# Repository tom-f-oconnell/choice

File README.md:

### Installation
1. [Install ROS Kinetic](http://wiki.ros.org/kinetic/Installation) on a supported operating system.  
   - Tested on [Ubuntu 16.04](https://www.ubuntu.com/download/desktop).
   - You can install Ubuntu alongside Windows with minimal effort.
   - Other ROS versions may work, but tested with Kinetic.
   - You only need `ros-kinetic-ros-base`.
      - You do *NOT* need everything in `ros-kinetic-desktop-full`, and it takes more disk space and install time.

2. Install the catkin packages.
   See ROS [tutorial on making a catkin workspace](http://wiki.ros.org/catkin/Tutorials/create_a_workspace).

   If you have not already, add a line to your `~/.bashrc` that loads the development setup script (that catkin generates), such as:
   ```
   source <your_catkin_workspace>/devel/setup.bash
   ```

   Then this should install all the packages you need:
   ```
   cd <your_catkin_workspace>/src
   git clone https://github.com/tom-f-oconnell/multi_tracker.git
   git clone https://github.com/tom-f-oconnell/usb_cam.git
   git clone https://github.com/tom-f-oconnell/rosserial.git
   git clone https://github.com/tom-f-oconnell/metatools.git
   git clone https://github.com/tom-f-oconnell/stimuli.git
   git clone https://github.com/tom-f-oconnell/choice.git
   cd <your_catkin_workspace>
   catkin_make
   . ~/.bashrc
   ```

   The last line loads `<your_catkin_workspace>/devel/setup.bash` because of the line you added to your `~/.bashrc` in the previous step.

   On all of the computers in the Hong lab, the catkin workspace can be found at `~/catkin`, for whichever user account was used to run the experiments.

   Currently, only installation from source is supported. In the future, I would like to make this installable as a ROS package via apt, but that would likely also require the same of `multi_tracker`, and there are some technical reasons that won't be possible right now with ROS Kinetic.

3. Upload the firmware to an Arduino MEGA
   1. Download and unzip Arduino to a path you will remember, or locate it if already installed.
      - Version ~1.5 - 1.8.3 should definitely work. Nearby versions almost certainly also will. You should get error messages when compiling if things do not work, and if this is the case you may need to use a different version of Arduino.
      - Arduino older than or equal to 1.0 will likely not work.
      - I unzipped Arduino to my home directory, which came out as as `~/arduino-1.8.3`, which I will use as an example.
   2. `cd ~/arduino-1.8.3/libraries` (or wherever your Arduino is installed)
   3. `rm -rf ros_lib` (in case some libraries have already been generated)
   4. `rosrun rosserial_arduino make_libraries.py .`
   5. Symlink to `stimuli` and `multishock` libraries. You only need
      `multishock` if uploading code that relies on the shift-register based
      shock control hardware.

      (still from `~/arduino-1.8.3/libraries`)
      ```
      ln -s ~/catkin/src/stimuli/arduino/libraries/stimuli
      ln -s ~/catkin/src/choice/arduino/libraries/multishock
      ```

   6. If you Arduino IDE was open, close and re-open it.
      - *Make sure that you are opening the same version of Arduino you installed the libraries for.* It is easier to only have one version of Arduino installed at any given time to avoid these conflicts.

   7. Add your user to the `dialout` group (if on Ubuntu), to be able to upload code.
      - `sudo adduser <username> dialout`
      - Log out and back in for the change to take effect

   8. Connect your Arduino MEGA to the computer.
      - Arduino's with less memory will currently **NOT** work, as there is considerable overhead in the generated ROS libraries.

   9. Upload code 
       
      For the basic stimulus delivery, open `File->Examples->stimuli->stimuli` 
      In the Arduino IDE, under the `Tools` menu:
      - Select appropriate port
         - Usually `/dev/ttyUSBX`, where `X` could vary. `/dev/ttyACMX` may also work. It is never the one like `/dev/ttyS0`.
         - May have the correct board model in parentheses after the port name
      - Select appropriate board (probably `Arduino/Genuino Mega or Mega 2560`)
      - Press the Upload button in the top left of the IDE
         - It looks like a circle with a righward arrow in it.
      - If the TX / RX lights flash on the Arduino, and the Upload seems to finish, you should be good to go.

4. *(Optional)* Set an alias for running `roslaunch` with a different `ROS_HOME` environment variable.

To load the configuration files from (and to save the output directory to) the current directory, I prefix the `roslaunch choice choice.launch` command with `ROS_HOME=``pwd```. To make all `roslaunch` invokations behave this way, which works for my purposes, you can make an alias for `roslaunch`.

If you don't already have a ~/.bash_aliases file, you can create one by opening it in a text editor, otherwise just open the file you already have. Add a line that says:
```
alias roslaunch='ROS_HOME=`pwd` roslaunch'
```

Save and close the file, and reload your terminal environment by typing `. ~/.bashrc`, or opening a new terminal. Now you can just type `roslaunch choice choice.launch`, and it will load configuration input from the current directory and save output there as well.

### Manufacture

TODO link to a readme in the design folder / wiki?

### Running an experiment

#### Requirements
The current directory has at least the following configuration files:
##### For tracking
- tracker_parameters.yaml
- roi_finder.yaml
- delta_video_parameters.yaml

- If running the tracking in real-time, also:
   - liveviewer_parameters.yaml
   - data_association_parameters.yaml
   - kalman_parameters.py

##### For stimulus
- stimulus_parameters.yaml

Depending on the camera you are using, you may also want to include parameters for your camera node, which you will have to load separately. There are some examples in the `multi_tracker` repository.

To copy templates for each of these configuration files to your current directory:
```
rosrun choice copy_configs.py
```

##### To set the length of the experiment
In the `stimulus_parameters.yaml` file, set the parameters starting at `olf/training_blocks` and ending at `olf/beyond_posttest_s` to appropriate values.

In `tracker_parameters.yaml`, set `multi_tracker/record_length_hours` to -1, so
that the length of the recording is determined by the stimulus presentation.

#### To run a full experiment with real-time tracking on the same computer.
Requires a computer with adequate memory and processor.
```
roslaunch choice choice.launch
```

##### Errors (red text)
The only error message that is normal during startup is one along the lines of `Parameter stimulus_arduino/debug does not exist`. Another other red text means something is likely not working, and you should not ignore it.

##### Warnings (yellow text)
`Failed to get param: timeout expired` is normal, as long as the program ultimately stops 
emitting these warnings. You should be aware of the reasons other warnings occur. 
Contact Tom with any questions.

#### To run an experiment saving a background subtracted video in a ROS bag file, for offline tracking.
Less hardware demands.
```
roslaunch choice choice.launch video_only:=True
```

##### Possible problems

If you run `rosparam list` before starting an experiment, you should see
`ERROR: Unable to communicate with master!`, otherwise, the existing parameters
can misconfigure any experiments you try to run.

First, check it isn't a valid experiment being run on another account, if you're
sharing the computer. If not, you should be able to stop the existing `roscore`
process with:
```
sudo pkill rosmaster
```

After this command, you another `rosparam list` should give you
```
ERROR: Unable to communicate with master!
```

### Stimulus Validation

To run the stimulus presentation that would happen during an experiment, but without any 
recording or tracking. For measurement / verification / PID purposes.
```
roslaunch choice choice.launch stimuli_only:=True
```

To run simpler pulse trains of a given duration, without changing the code on the Arduino. 
This launch file will also look for a `stimulus_parameters.yaml` file in the same path, but
with slightly different parameters.
```
roslaunch stimuli pid.launch seconds:=30
```

See [this repo](https://github.com/tom-f-oconnell/stimuli#validation) for more information 
on the parameters and launch file arguments for `pid.launch`.

To test the valves (I run this before and after each experiment, to make sure no connections came loose. With more robust electronics this might be less of a concern.)
- The number of the pin to be switched will be printed in the terminal you run the launch file from.
- I attach higher pressure air to all valves and check manually for air flow at each pin that should be switched.
```
roslaunch stimuli test_valves.launch
```

Press `<Ctrl>-C` to stop the `test_valves.launch` file.

### Offline tracking

#### Requirements
- The environment variable `DATA_DIR` is set to a path you will keep your data directories beneath.
   - I organize my experiment directories as grandchildren of `DATA_DIR`, grouping them as I see fit with directories (of arbitrary names) just beneath `DATA_DIR`.
   - To test that this is set, you can run `echo $DATA_DIR`, and the path should be printed.
   - To set this:

     Add a line to your `~/.bashrc` file like:

     ```
     export DATA_DIR="<full_path_to_data_directory>"
     ```

     For instance, mine has this line:
     ```
     export DATA_DIR="$HOME/data"
     ```

     Then, either start a new terminal, or run `. ~/.bashrc`, so that the change in the environment variable takes effect.

- `$DATA_DIR/retracked` exists and has all of the configuration files required for tracking (see requirements for running an experiment above)
- All of the installation instructions for at least ROS and the `multi_tracker` package are done.

On any computer satisfying these requirements, run:
```
rosrun multi_tracker retrack_ros <experiment_directory> <decimal_valued_rate>
```

The `<decimal_valued_rate>` can be set as high as does not produce a stream of warning messages that does not improve until the tracking finishes.  If the computer appears to be straining, you may also want to decrease the rate.  If you want to also employ more limited computers for tracking lots of data, you are also able to decrease the rate beneath 1.0 if necessary.

The default rate is currently 0.8, if no rate is provided. Our analysis workstations can track up to a rate of 4.0 - 5.0, with little issue.

The `<experiment_directory>` can be any of:
- ~~a path to a valid directory~~
- ~~a file within a valid directory~~
- the name of a subdirectory beneath `$DATA_DIR`, if the `DATA_DIR` environment variable is set
   - the way this script currently finds the output path, it requires `DATA_DIR`, so you should use this option for now.

A valid directory has:
- at a minimum:
   - a name in the `YYYYMMDD_HHMMSS` format
   - a bag file
   - any background PNGs that were in the same directory
   - a file with the ROIs called `compressor_rois_<experiment_id>.yaml`
- ideally, all files generated during acquisition, including also:
   - a `*_parameters.yaml` file
   - a `*_stimuli.p` file

#### Example
```
rosrun multi_tracker retrack_ros 20170930_164433 2.0
```

In this example, `DATA_DIR` was set with a line in my `~/.bashrc` file as:
```
export DATA_DIR="$HOME/data"
```
and `/home/tom/data/20170920/20170930_164433` was a valid directory. Note that `20170930_164433` was not a direct child directory of `DATA_DIR`. The code may currently expect the `<experiment_directory>` to be a granchild of `DATA_DIR`, if this option is selected.

#### Output
After running the tracking, the valid directory you provided as input will also have:
- An HDF5 file with a the variables the tracker is estimating, over time
   - The `position_x` and `position_y`

#### Copying data from acquisition to tracking / analysis computer

You are of course free to copy the files via other means. This may just end up being convenient.

#### Requirements
- Both computers have internet access
- The computer you are trying to connect TO has an SSH server installed and running
   - Look up how to install OpenSSH server for the operating system you are using if you need to do this.

```
rsync -auvPzr <folder_with_data> user@<server_ip_address>:~/<place_to_put_it>
```

The rsync command with those flags seems not to work if you include a trailing slash after the `<folder_with_data>` name.

#### Example
```
rsync -auvPzr ~/data/. tom@gerty:~/data
```
This example will recursively copy all subdirectories of data, and I keep all my experiment directories nested within here.

#### Known bugs + workarounds
If you notice your computer working harder than it should when the acquisition / tracking should otherwise have terminated, you can run `top` or some other process manager, and check for a handful of processes, owned by the same user that ran the launch file, with names including:
- `play`
- `record`
- `python`
- `<something>launch` ?

And assuming you are OK killing all ROS processes currently running on your computer, you can try running:
- `killall roscore`
- `killall roslaunch`
- `killall play`

Under some circumstances, you may also want to kill all python processes owned by the user that started the ROS processes, with `killall python`.

### Analysis
#### Requirements
(To be added )
- `DATA_DIR` is set as in offline tracking instructions.
- `choice` and `multi_tracker` are installed as above (though you don't technically need all of ROS)
- The experiments you want to analyze together have their data folders grouped within an immediate subdirectory of `$DATA_DIR/retracked`.
   - If your tracking output comes from real-time tracking, it does not need to be treated differently, apart from copying it to a subdirectory beneath `$DATA_DIR/retracked`.
- The `ruamel.yaml` package, which you should be able to get via:
   ```
   cd <choice>
   pip install -r requirements.txt
   ```
   Again, if you need root access to install via `pip`, use `sudo` as above.

#### Running
```
rosrun choice choice_analysis <subdirectory>
```

If, across all analysis runs *that have used this folder as input*, you have not already labelled all experiments as either good or needing rejection for some reason, a GUI should open asking you to label the traces appropriately. See the terminal output for which keys correspond to which labels.

The output of this labelling should be saved as `$DATA_DIR/retracked/<subdirectory>/analysis_rejects.yaml`. It is human readable, and you can edit it by hand in a text editor if you want to change something. If you want to start the labelling over, feel free to delete or move / rename `analysis_rejects.yaml`.

Currently, if you want labels to apply across groupings of your data, (across analysis runs with different subdirectories as input) you will need to manually merge the `analysis_rejects.yaml` text files.

#### Output

Within the `$DATA_DIR/retracked/<subdirectory>`, you should find a number of files in a graphics format (svg by default). For each odor, each reject category, and each preference metric (fraction of time spent and "decision bias"), you will find:
- `<metric>.svg`
   - For pooled data of all non-rejects, across all odors.
- `<odor>_<metric>.svg` (or .other_graphic_format, like .png)
   - For pooled data of all non-rejects, within an odor.
- `<reject_category>_<metric>.svg`
   - For data of all rejects of a certain label / category, pooled across odors

There will also be text output, in the terminal in which you ran the analysis, describing the metrics within and across odors, and the fraction of flies in each reject category.

### Updating code

If you have made any changes to your local copies of these repositories that you would like to keep, look up `git stash` and proceed with caution, otherwise:

```
roscd multi_tracker
git pull
roscd choice
git pull
```

Then, repeat the instructions for installing catkin packages above, which should look like:
```
cd <catkin_workspace>
catkin_make
. ~/.bashrc
```

This, again, requires that you have a line in your `~/.bashrc` that "sources" (loads) the file `<catkin_ws>/devel/setup.bash`, or else the line `. ~/.bashrc` will not necessarily apply all updates that have been made to the code.

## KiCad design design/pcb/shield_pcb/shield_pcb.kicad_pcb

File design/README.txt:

If any .svg or .fcstd files are newer than files of the same name with a
different extension (should be .eps and .stl, respectively), then you may want
to delete those .eps and .stl files and re-generate them from the newer source
files before cutting / printing the parts.

SVGs are Inkscape SVGs. Generally I would export these as EPS and then load them
on the computer connected to the laser cutter in Coreldraw.  In Coreldraw, I
would convert all lines to "Hairline" , as this was required for any lines you'd
like to cut (<0.0001" should be treated the same, but it is harder to work with
while designing).

.fcstd files should be openable with FreeCAD. The software is getting a lot
better, so it is worth getting the most recent version from the PPA (you can
look up how to do this). I generally used version 0.17. To export STLs you have
to open the FCSTD file, select an object (on the left, the highest level node
that isn't the name of the document), and then go to File->Export and change the
output file type to STL.  I prepared gcode (instruction for the 3D printer) in
Cura, on Windows, because this is what our librarian showed me how to use.

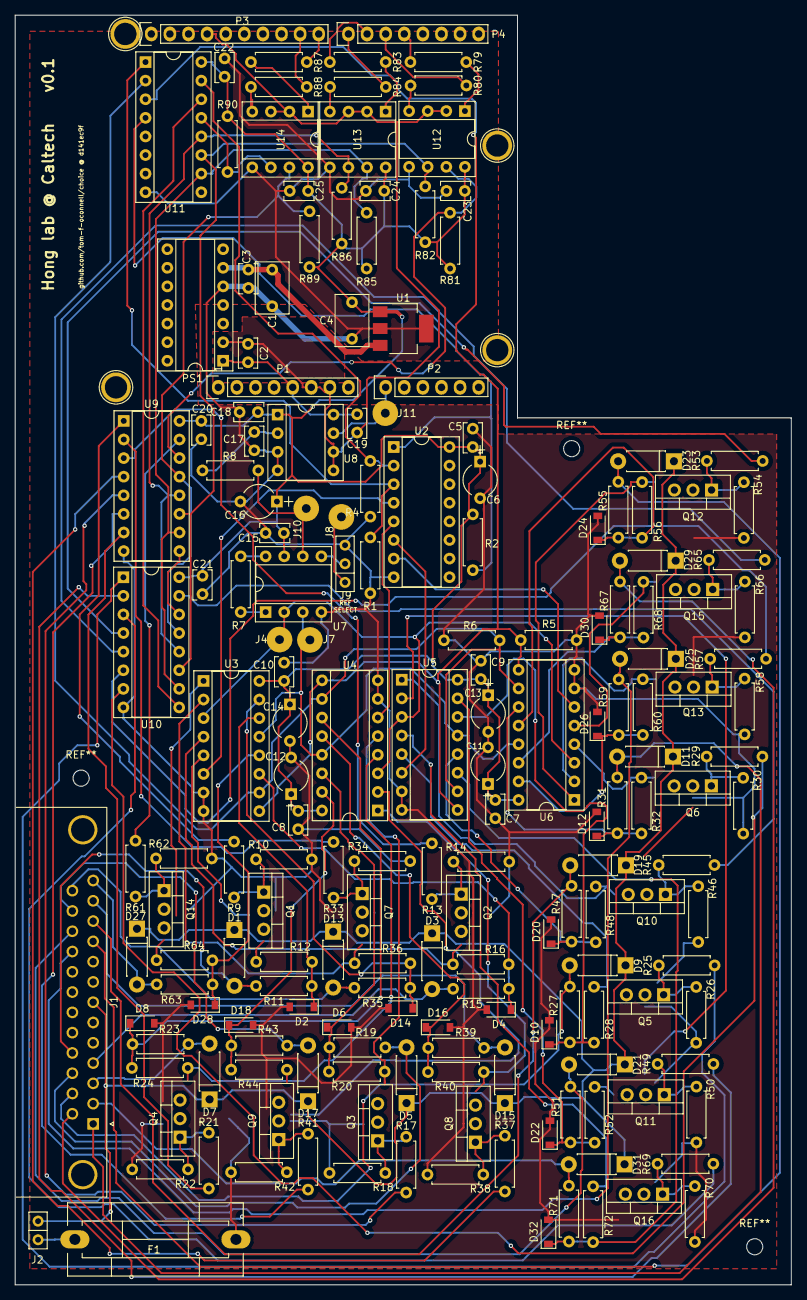
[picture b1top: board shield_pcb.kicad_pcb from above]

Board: 2 copper layers, 106.0 x 173.4 mm, 188 parts (0 on the bottom side), 125 nets.

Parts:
C1, C4: 1uF; C_Rect_L7.0mm_W4.5mm_P5.00mm
C2, C3: 2.2uF; C_Rect_L4.0mm_W2.5mm_P2.50mm
C5, C7, C8, C9, C10, C15, C18, C19, C20, C21, C22, C23, C24, C25: 0.1uF; C_Rect_L4.0mm_W2.5mm_P2.50mm
C6, C11, C12, C13, C14, C16: 10uF; CP_Radial_Tantal_D4.5mm_P5.00mm
C17: 22nF; C_Rect_L4.0mm_W2.5mm_P2.50mm
D1, D3, D5, D7, D9, D11, D13, D15, D17, D19, D21, D23, D25, D27, D29, D31: D; D_DO-41_SOD81_P7.62mm_Horizontal
D2, D4, D6, D8, D10, D12, D14, D16, D18, D20, D22, D24, D26, D28, D30, D32: MMSZ5231B; D_SOD-123
F1: Fuse; Fuseholder5x20_horiz_SemiClosed_Casing10x25mm
J1: DB25_Female; DSUB-25_Female_Horizontal_Pitch2.77x2.84mm_EdgePinOffset7.7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
J2: Screw_Terminal_01x02; SIP-2_terminal_block
J4, J7, J8, J10, J11: Conn_01x01; SolderWirePad_single_1-2mmDrill
J9: Conn_01x03_Male; SIP-3
P1: Power; Socket_Strip_Arduino_1x08
P2: Analog; Socket_Strip_Arduino_1x06
P3: Digital; Socket_Strip_Arduino_1x10
P4: Digital; Socket_Strip_Arduino_1x08
P5, P6, P7, P8: CONN_01X01; Arduino_1pin
PS1: DCP020507P; DIP-14_W7.62mm_Socket
Q1, Q2, Q3, Q4, Q5, Q6, Q7, Q8, Q9, Q10, Q11, Q12, Q13, Q14, Q15, Q16: IRL620; TO-220-3_Vertical
R1, R2, R4, R5, R6: 4.7K; R_Axial_DIN0207_L6.3mm_D2.5mm_P7.62mm_Horizontal
R7: R; R_Axial_DIN0207_L6.3mm_D2.5mm_P7.62mm_Horizontal
R8: 10; R_Axial_DIN0207_L6.3mm_D2.5mm_P7.62mm_Horizontal
R9, R13, R17, R21, R25, R29, R33, R37, R41, R45, R49, R53, R57, R61, R65, R69: 150; R_Axial_DIN0207_L6.3mm_D2.5mm_P7.62mm_Horizontal
R10, R12, R14, R16, R18, R20, R22, R24, R26, R28, R30, R32, R34, R36, R38, R40, R42, R44, R46, R48, R50, R52, R54, R56, R58, R60, R62, R64, R66, R68, R70, R72: 100K; R_Axial_DIN0207_L6.3mm_D2.5mm_P7.62mm_Horizontal
R11, R15, R19, R23, R27, R31, R35, R39, R43, R47, R51, R55, R59, R63, R67, R71: 39K; R_Axial_DIN0207_L6.3mm_D2.5mm_P7.62mm_Horizontal
R79, R80, R83, R84, R87, R88: 220; R_Axial_DIN0207_L6.3mm_D2.5mm_P7.62mm_Horizontal
R81, R82, R85, R86, R89, R90: 2.2K; R_Axial_DIN0207_L6.3mm_D2.5mm_P7.62mm_Horizontal
U1: LT1118-5; SOT-223
U2: 4556; DIP-16_W7.62mm_Socket
U3, U4, U5, U6: CD4052B; DIP-16_W7.62mm_Socket
U7: AD623; DIP-8_W7.62mm_Socket
U8: ACPL-790x; DIP-8_W7.62mm_Socket
U9, U10, U11: 74HC595; DIP-16_W7.62mm_Socket
U12, U13, U14: TLP2531; DIP-8_W7.62mm_Socket

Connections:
+5V: C2.1, C19.2, P1.5, PS1.1, U8.8
+5VA: C4.1, C5.1, C6.1, C7.1, C8.1, C9.1, C10.1, C11.1, C12.1, C13.1, C14.1, C15.1, C16.1, C18.1, C20.1, C21.1, C22.1, C23.1, C24.1, C25.1, R2.1, R81.1, R82.1, R85.1, R86.1, R89.1, R90.1, U1.1, U2.16, U3.16, U4.16, U5.16, U6.16, U7.7, U8.1, U9.16, U10.16, U11.16, U12.8, U13.8, U14.8
/1+: D28.1, R63.2, R64.1, U3.12
/1-: Q14.2, R64.2, U3.1
/2+: D2.1, R11.2, R12.1, U3.14
/2-: Q1.2, R12.2, U3.5
/3+: D14.1, R35.2, R36.1, U3.15
/3-: Q7.2, R36.2, U3.2
/4: P4.4, R79.2
/4+: D4.1, R15.2, R16.1, U3.11
/4-: Q2.2, R16.2, U3.4
/5(**): P4.3, R80.2
/5+: D16.1, R39.2, R40.1, U4.12
/5-: Q8.2, R40.2, U4.1
/6(**): P4.2, R83.2
/6+: D6.1, R19.2, R20.1, U4.14
/6-: Q3.2, R20.2, U4.5
/7: P4.1, R84.2
/7+: D18.1, R43.2, R44.1, U4.15
/7-: Q9.2, R44.2, U4.2
/8: P3.10, R87.2
/8+: D8.1, R23.2, R24.1, U4.11
/8-: Q4.2, R24.2, U4.4
/9(**): P3.9, R88.2
/9+: D20.1, R47.2, R48.1, U5.12
/9-: Q10.2, R48.2, U5.1
/10+: D10.1, R27.2, R28.1, U5.14
/10-: Q5.2, R28.2, U5.5
/11+: D22.1, R51.2, R52.1, U5.15
/11-: Q11.2, R52.2, U5.2
/12+: D32.1, R71.2, R72.1, U5.11
/12-: Q16.2, R72.2, U5.4
/13+: D24.1, R55.2, R56.1, U6.12
/13-: Q12.2, R56.2, U6.1
/14+: D30.1, R67.2, R68.1, U6.14
/14-: Q15.2, R68.2, U6.5
/15+: D26.1, R59.2, R60.1, U6.15
/15-: Q13.2, R60.2, U6.2
/16+: D12.1, R31.2, R32.1, U6.11
/16-: Q6.2, R32.2, U6.4
/A0: J11.1, P2.1, U8.7
/CA: R6.1, U3.10, U4.10, U5.10, U6.10, U11.2
/CB: R5.1, U3.9, U4.9, U5.9, U6.9, U11.3
/DA: R4.1, U2.2, U11.15
/DB: R1.1, U2.3, U11.1
/DMUX_EN: R2.2, U2.1, U11.4
/F1: D27.2, J1.13, R63.1
/F2: D1.2, J1.17, R11.1
/F3: D13.2, J1.25, R35.1
/F4: D3.2, J1.4, R15.1
/F5: D15.2, J1.12, R39.1
/F6: D5.2, J1.16, R19.1
/F7: D17.2, J1.24, R43.1
/F8: D7.2, J1.3, R23.1
/F9: D19.2, J1.11, R47.1
/F10: D9.2, J1.15, R27.1
/F11: D21.2, J1.23, R51.1
/F12: D31.2, J1.2, R71.1
/F13: D23.2, J1.10, R55.1
/F14: D29.2, J1.14, R67.1
/F15: D25.2, J1.22, R59.1
/F16: D11.2, J1.1, R31.1
/IN1: R61.2, U9.15
/IN2: R9.2, U9.1
/IN3: R33.2, U9.2
/IN4: R13.2, U9.3
/IN5: R37.2, U9.4
/IN6: R17.2, U9.5
/IN7: R41.2, U9.6
/IN8: R21.2, U9.7
/IN9: R45.2, U10.15
/IN10: R25.2, U10.1
/IN11: R49.2, U10.2
/IN12: R69.2, U10.3
/IN13: R53.2, U10.4
/IN14: R65.2, U10.5
/IN15: R57.2, U10.6
/IN16: R29.2, U10.7
/digital_input_isolation/optoisolator_with_peripherals_1/out_1: R81.2, U9.14, U12.7
/digital_input_isolation/optoisolator_with_peripherals_1/out_2: R82.2, U9.11, U10.11, U11.11, U12.6
/digital_input_isolation/optoisolator_with_peripherals_2/out_1: R85.2, U9.10, U10.10, U11.10, U13.7
/digital_input_isolation/optoisolator_with_peripherals_2/out_2: R86.2, U9.12, U10.12, U11.12, U13.6
/digital_input_isolation/optoisolator_with_peripherals_3/out_1: R89.2, U9.13, U10.13, U14.7
/digital_input_isolation/optoisolator_with_peripherals_3/out_2: R90.2, U11.13, U14.6
GND: C2.2, C19.1, P1.6, P1.7, P3.4, PS1.2, U8.5, U8.6, U12.2, U12.3, U13.2, U13.3, U14.2, U14.3
GNDA: C1.1, C3.2, C4.2, C5.2, C6.2, C7.2, C8.2, C9.2, C10.2, C11.2, C12.2, C13.2, C14.2, C15.2, C16.2, C17.2, C18.2, C20.2, C21.2, C22.2, C23.2, C24.2, C25.2, D2.2, D4.2, D6.2, D8.2, D10.2, D12.2, D14.2, D16.2, D18.2, D20.2, D22.2, D24.2, D26.2, D28.2, D30.2, D32.2, F1.1, J9.3, PS1.5, Q1.3, Q2.3, Q3.3, Q4.3, Q5.3, Q6.3, Q7.3, Q8.3, Q9.3, Q10.3, Q11.3, Q12.3, Q13.3, Q14.3, Q15.3, Q16.3, R1.2, R4.2, R5.2, R6.2, R10.2, R14.2, R18.2, R22.2, R26.2, R30.2, R34.2, R38.2, R42.2, R46.2, R50.2, R54.2, R58.2, R62.2, R66.2, R70.2, U1.2, U1.4, U2.8, U3.7, U3.8, U4.7, U4.8, U5.7, U5.8, U6.7, U6.8, U7.4, U8.3, U8.4, U9.8, U10.8, U11.8, U12.5, U13.5, U14.5
HV: D1.1, D3.1, D5.1, D7.1, D9.1, D11.1, D13.1, D15.1, D17.1, D19.1, D21.1, D23.1, D25.1, D27.1, D29.1, D31.1, J1.7, J2.1
unnamed: C1.2, C3.1, PS1.6, U1.3
unnamed: C17.1, R8.1, U8.2
unnamed: F1.2, J2.2
unnamed: J4.1, U3.3, U4.3, U5.3, U6.3, U7.2
unnamed: J7.1, U3.13, U4.13, U5.13, U6.13, U7.3
unnamed: J8.1, J9.1
unnamed: J9.2, U7.5
unnamed: J10.1, R8.2, U7.6
unnamed: Q1.1, R9.1, R10.1
unnamed: Q2.1, R13.1, R14.1
unnamed: Q3.1, R17.1, R18.1
unnamed: Q4.1, R21.1, R22.1
unnamed: Q5.1, R25.1, R26.1
unnamed: Q6.1, R29.1, R30.1
unnamed: Q7.1, R33.1, R34.1
unnamed: Q8.1, R37.1, R38.1
unnamed: Q9.1, R41.1, R42.1
unnamed: Q10.1, R45.1, R46.1
unnamed: Q11.1, R49.1, R50.1
unnamed: Q12.1, R53.1, R54.1
unnamed: Q13.1, R57.1, R58.1
unnamed: Q14.1, R61.1, R62.1
unnamed: Q15.1, R65.1, R66.1
unnamed: Q16.1, R69.1, R70.1
unnamed: R7.1, U7.1
unnamed: R7.2, U7.8
unnamed: R79.1, U12.1
unnamed: R80.1, U12.4
unnamed: R83.1, U13.1
unnamed: R84.1, U13.4
unnamed: R87.1, U14.1
unnamed: R88.1, U14.4
unnamed: U2.4, U3.6
unnamed: U2.5, U4.6
unnamed: U2.6, U5.6
unnamed: U2.7, U6.6
unnamed: U10.9, U11.14
unnamed: U9.9, U10.14

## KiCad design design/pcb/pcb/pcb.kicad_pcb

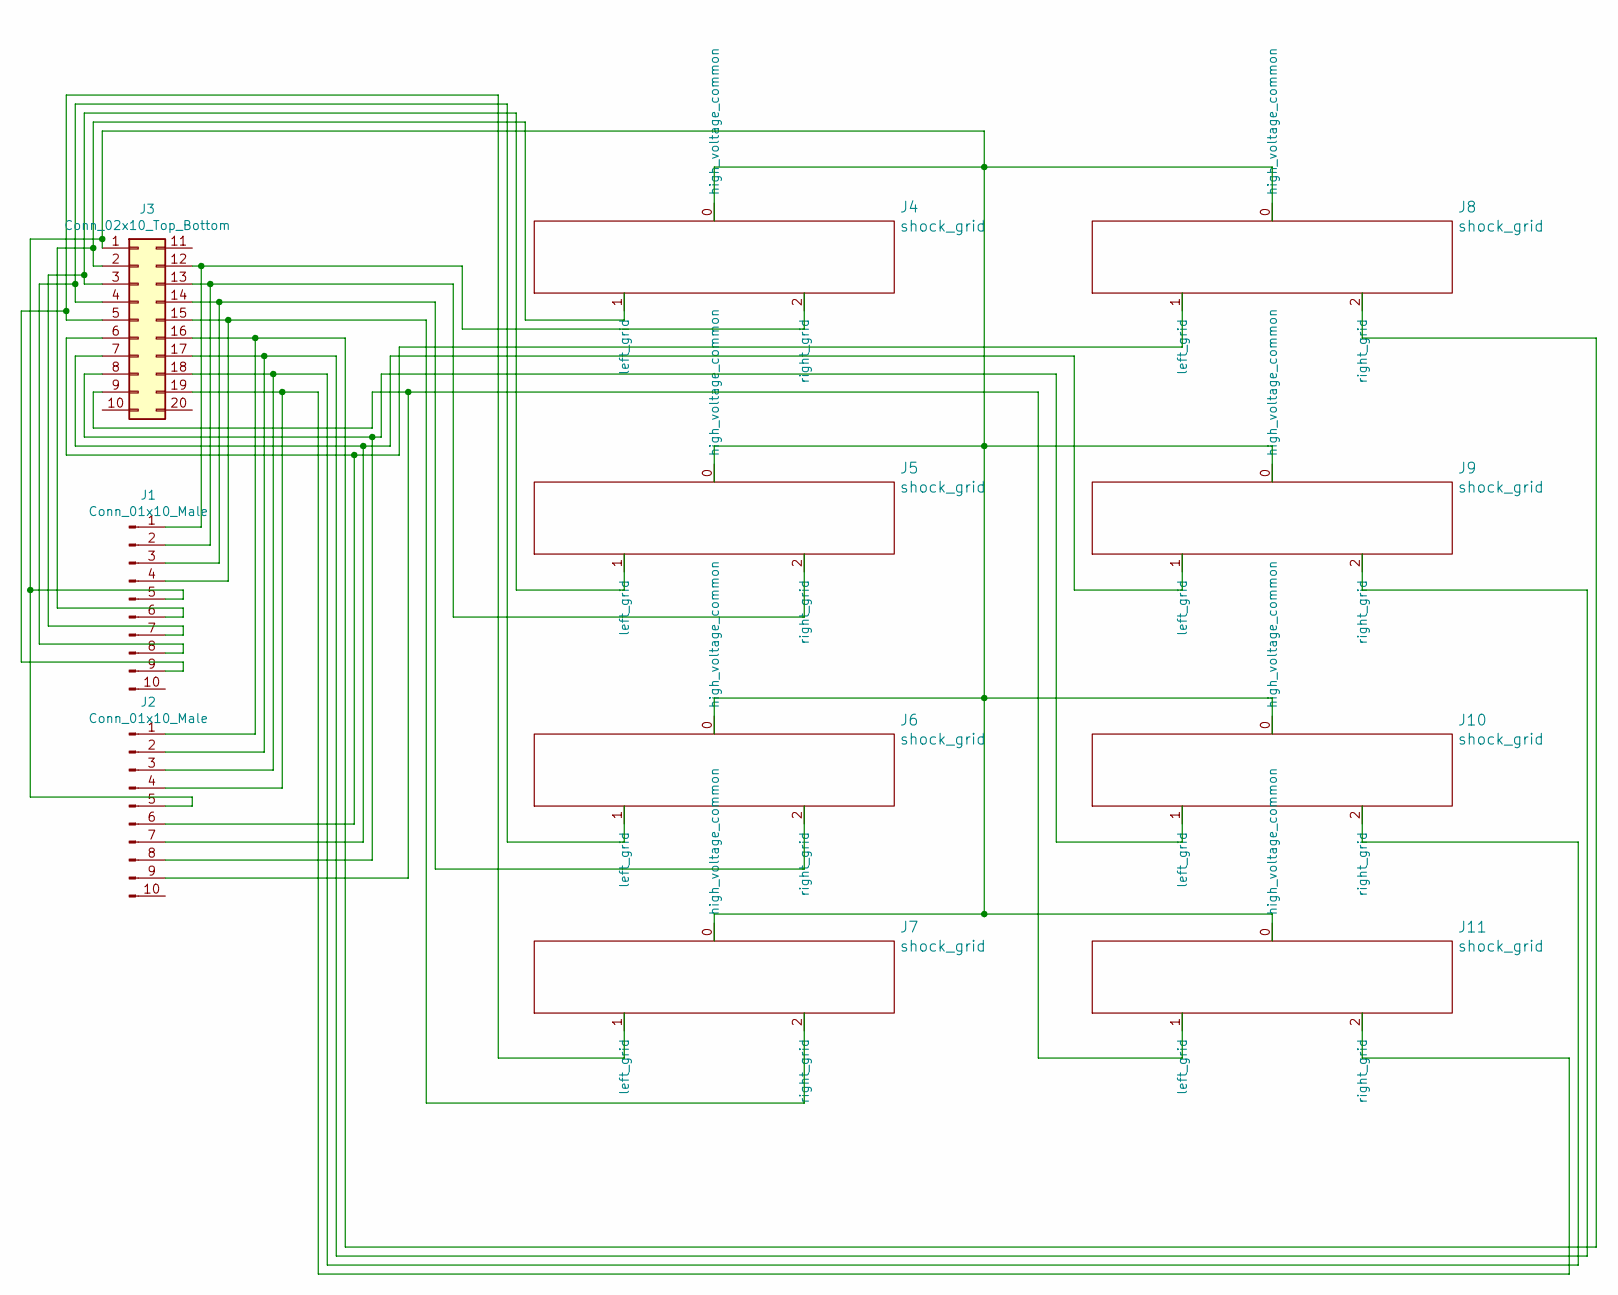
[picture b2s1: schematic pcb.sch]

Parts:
J1, J2: Conn_01x10_Male; SIP-10_2.54mm_1mm_clearance
J3: Conn_02x10_Top_Bottom; DIP-2x10_2.54mm_1mm_clearance
J4, J5, J6, J7, J8, J9, J10, J11: shock_grid; electrode

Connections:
unnamed: J1.1, J3.12, J4.2 (right_grid)
unnamed: J1.2, J3.13, J5.2 (right_grid)
unnamed: J1.3, J3.14, J6.2 (right_grid)
unnamed: J1.4, J3.15, J7.2 (right_grid)
unnamed: J1.5, J2.5, J3.1, J4.0 (high_voltage_common), J5.0 (high_voltage_common), J6.0 (high_voltage_common), J7.0 (high_voltage_common), J8.0 (high_voltage_common), J9.0 (high_voltage_common), J10.0 (high_voltage_common), J11.0 (high_voltage_common)
unnamed: J1.6, J3.2, J4.1 (left_grid)
unnamed: J1.7, J3.3, J5.1 (left_grid)
unnamed: J1.8, J3.4, J6.1 (left_grid)
unnamed: J1.9, J3.5, J7.1 (left_grid)
unnamed: J2.1, J3.16, J8.2 (right_grid)
unnamed: J2.2, J3.17, J9.2 (right_grid)
unnamed: J2.6, J3.6, J8.1 (left_grid)
unnamed: J2.7, J3.7, J9.1 (left_grid)
unnamed: J2.8, J3.8, J10.1 (left_grid)
unnamed: J2.3, J3.18, J10.2 (right_grid)
unnamed: J2.9, J3.9, J11.1 (left_grid)
unnamed: J2.4, J3.19, J11.2 (right_grid)

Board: 2 copper layers, 11 parts (0 on the bottom side), 17 nets, no tracks yet.

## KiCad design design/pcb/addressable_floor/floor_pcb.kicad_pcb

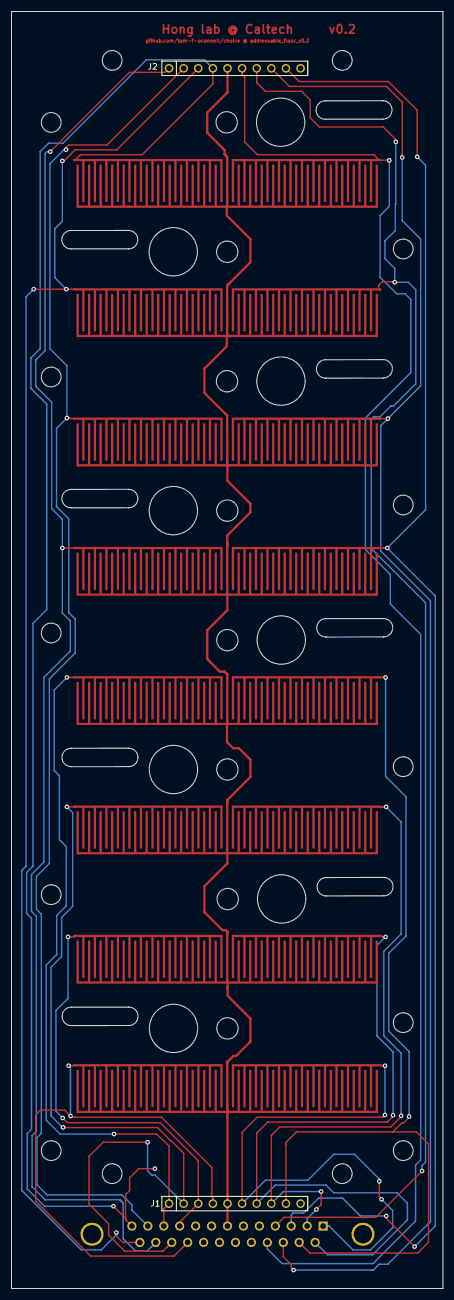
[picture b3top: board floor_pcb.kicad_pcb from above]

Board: 2 copper layers, 75.0 x 222.0 mm, 11 parts (1 on the bottom side), 17 nets.

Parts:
J1, J2: Conn_01x10_Male; SIP-10_2.54mm_1mm_clearance
J3: DB25_Male; DSUB-25_Male_Horizontal_Pitch2.77x2.84mm_EdgePinOffset7.70m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
J4, J5, J6, J7, J8, J9, J10, J11: shock_grid; electrodes_clearance0.6mm_W0.4mm_centerflush

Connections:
/F1: J2.4, J3.13, J11.2
/F2: J2.6, J3.17, J11.1
/F3: J2.3, J3.25, J10.2
/F4: J2.7, J3.4, J10.1
/F5: J2.2, J3.12, J9.2
/F6: J2.8, J3.16, J9.1
/F7: J2.1, J3.24, J8.2
/F8: J2.9, J3.3, J8.1
/F9: J1.1, J3.11, J7.2
/F10: J1.9, J3.15, J7.1
/F11: J1.2, J3.23, J6.2
/F12: J1.8, J3.2, J6.1
/F13: J1.3, J3.10, J5.2
/F14: J1.7, J3.14, J5.1
/F15: J1.4, J3.22, J4.2
/F16: J1.6, J3.1, J4.1
/HV: J1.5, J2.5, J3.7, J4.0, J5.0, J6.0, J7.0, J8.0, J9.0, J10.0, J11.0

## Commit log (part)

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2017-06-14 Initial commit. Will probably redesign bottom plate and vacuum trap sliders, to facilitate mounting and move motors out of lighting path.
2017-06-15 Need to finish adding sorter support in Arduino script. Also likely need to make more of it non-blocking.
2017-06-17 Added all material Allie compiled (downloaded from Hong lab NAS) to design/reference. Added attribution.
2017-06-22 Actually added initial files re: shaft doubler for sorters.
2017-06-28 Made vacuum trap flow feature a polyline to try to fill in Coreldraw. Might hurt things later.
2017-06-29 First draft without glue necessary to seal sliders (ideally). Hoses coming out of bottom. Slot in bottom plate to accomodate.
2017-06-30 Added hole for screw in servo arm.
2017-08-09 Initial thoughts on some python nodes I'd need. Likely won't use.
2017-08-09 Added swp files to gitignore
2017-08-14 Initial (untested) draft of stimuli generator and the class that communicates that to the Arduino node.
2017-08-19 Launch file contains working invocation of versionpub.
2017-08-23 Added beginning of parameter validator configuration yaml file, and starting working on analysis code under src/ (I may have to rename it).
2017-09-03 Made default port /dev/ttyACM0, uniqueified pins before making list of DefaultStates, added Arduino debug flag to testing.yaml
2017-09-09 Refactored to work with new message types in services, forced by bug in rosserial.
2017-09-10 Fixed bug in odor_randomizer_choice causing wrong ITI / no following test. Removed TODOs from stimulus_parameters.
2017-09-14 Using right dimension now, but bounds and center of arena could probably be set better.
2017-09-15 Data centered, patches showing correctly with legend. Still need to check sides aren't flipped in some places and filter bad data.
2017-09-15 Orientation of plot / colored rectangles overlayed for odors / video, should all be the same in the ways that really matter now.
2017-09-18 Added clamps to delrin_chambers_and_manifold. Not sure what changes were made to other file... CHECK
2017-09-19 Fixed some left / right odor handling, and removed notes from comment blocks (put in data/retracked/notes.txt)
2017-09-20 Changed the display settings to be somewhat more to my liking. Still not a huge fan of colors for odors. Need to make subplots by keep / rejection type.
2017-09-20 Added backup requirements (not complete now). Summary plots mostly OK.
2017-09-21 Starting testing out Evernote API, but having authentication problems.
2017-09-25 Fixed skipping of trajectories already labelled in analysis_rejects.yaml file.
2017-09-25 Generating DataFrame in analysis function containing a few basic variables about traces. Want to add more about conditions of fly / time of experiment. Want to factor metric change function out for f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
2017-09-27 Coopted want_<metric> flags to include whether should be calculated, finished first iter of decision bias stuff, added version printing w/ git.
2017-09-28 Added histograms for changes in metrics of interest.
2017-10-02 lsof based checking rsync finishes that I thought was already on the other analysis computer...
2017-10-03 Added code to print report for weekly log of experiment progress.
2017-10-05 Fixed (though not cleanest) handling of # train blocks = 0 (should work, without training).
2017-10-10 Added initial support for innate bias experiments.
2017-10-18 Added DXFs exported from PCBArtist, using contents of ZIPs as input.
2017-10-18 Trying to not have all the traces get squished, and testing fixed aspect ratio, but haven't looked at output yet.
2017-10-25 If any real changes, more changing grid blocks to route traces around pockets in the PCB. Will revert DXF to probably b610d1ea for import into KiCAD
2017-10-27 Electrode footprint seems more or less what I want. May need to change some things to get it to connect up appropriately with the traces.
2017-11-01 Made two custom (S/D)IP footprints with slightly larger clearances. Mostly fixed custom electrode footprint pad anchor points.
2017-11-06 Re-ordered some pins in sch and regenerated netlist. Increased y margin to connectors for extra space for routing. Finished routing of board with original footprint geometry.
2017-11-07 Updated launch file considering refactor to stimuli + recent rename. May still do some refactoring.
2017-11-08 Made analysis input path relative to /home/tom/data, for consistency with some tracking steps, and to not require people who otherwise followed the README to edit the script.
2017-11-10 Added Arduino MEGA microcontroller datasheet.
2017-11-10 Refactored (draft) of one unit into switch_and_signal. May remake parent from Arduino shield template.
2017-11-13 Fixed shield schematic, at least for KiCad <= d8f4e35. Added notes to single measurement unit. Updated IRL620 library part to include correct datasheet, etc.
2017-11-14 Picked AD623 instrumentation amplifer to be downstream of analog switches. I think I'm mostly done with demux to ADC subcircuit, apart from setting the gain and maybe some more decoupling caps. Added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
2017-11-24 Changed TODOs in schematic. Added some pull-up/downs (may revise). Added test code. Added .odt w/ all pin configs of ICs for reference in testing.
2017-11-27 Refactored test code to have different options behind defines (rather than commented). Added some datasheets mainly for mechanical info. Removed a lot of stuff I previously called optional in schemat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
2017-11-29 Finished a large portion of routing. May undo some of it to switch to >1-1.4mm clearance on at least the very input nets. Actually, maybe I won't... none of the other components are really designed t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
2017-12-05 Back imported autorouter output. Fixed DRC errors in Arduino inputs seemingly caused by numerical errors. Going to try to setup ground / power planes.
2017-12-06 Updated electrode_vertices.py to also generate electrodes interleaved along the long axis, for an orthogonal set of ceiling electrodes. New *_lengthwise footprint should be correct, if not a little w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
2017-12-06 v0.1 boards done. Decided not to add LEDs to shield board for now.
2017-12-12 Added script to generate OpenSCAD script, which can then generate a 3D model of the behavior chambers. TODO use similar approach to get PCB outlines for Kicad, integrate w/ Kicad 3D, workaround DXF l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
2017-12-12 package_files.sh is almost completely working to take Kicad output and produce ZIPs for Advanced Circuits (sends everything through gerbv for AC compliant formatting). Not sure why script is breaking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
2017-12-13 Added git ignores to both kicad project directories with parts, to ignore xml intermediate created during export to BoM.
2017-12-13 Made .pro file of floor slightly more similar to (ostensibly fixed correctly) shield. Same with caches.
2017-12-13 After loading changes into Eeschema and saving.
2017-12-14 Added install script for hole fixing kicad plugin.
2017-12-14 Towards the final stages of initial working hole conversion code.
2017-12-14 To be submitted for manufacture w/ Advanced Circuits BareBones
2017-12-16 Added some wishlist items to TODOs thinking about box to reorder parts for a clone, and after first looking at new PCBs. Perhaps more to come after (attempting to) assemble first board.
2017-12-29 Deleted unused freecad script, and added test DXF to see if any of the cutter software (inkscape / corel) can see the transparency in the R2013 DXF
2018-01-04 Resizing test units again.
2018-01-08 Added some TODOs
2018-01-09 TODOs, some current use measurements, and another shift register test. What are board changes?
2018-01-11 Added library.properties and EXAMPLE keywords.txt (Arduino lib metadata).
2018-01-12 Finished initial draft of arduino library. Update hpp, then start trying to compile and test.
2018-01-15 Added some unit tests. Fixing one.
2018-01-15 Fixed typo in a for loop, now compiling in Arduino environment.
2018-01-16 Just got test_fet_indexing apparently working. Required fixing update_registers. Compiling with SR_NODELAY now.
2018-01-23 Fixed bugs in test_demux_fet_indexing_match and after some hardware tweaking, one board is working! On to the amplifier circuitry / testing with flies.
2018-01-25 Updated testing to automatically register gtest tests with CTest + ./test script to make an run everything. In line with template in my gtest_template repo.
2018-01-30 Deleted unused src dir (was causing problems w/ rosserial message generation)
2018-01-31 Reformatting choice_analysis and minor changes to hopefully get it to work with one pin shock.
2018-02-07 Added initial code to plot currents from extra extra nodes that get this information off of the Arduino. Hard coded new pins into analysis + bugfix.
2018-02-14 Fixed lid for clear PCB that was too short to reach bottom contacts. Also made space in inner layers for top contact.
2018-02-20 Partially renamed ceiling_pcb to addressable_ceiling, and copied to open_loop_pcb, which I modified to be a simpler version of the former, now with only three electrodes (L/HV/R).
2018-02-22 Added design dilated in GIMP. May want to dilate more. To get more robust traces -> better yield.
2018-02-23 Moved analysis configuration up to the top for now. Will break out later.
2018-03-01 Fixed bug caused by omitting from __future__ import division
2018-03-27 Set of hacks to get trials with no stimuli to plot (for troubleshooting), plus fixed one range setting bug. Formatting and TODOs.
2018-03-27 Declared variables assigned in function as global. Other cases where this is necessary (check for assignment, I think). start still not defined in some cases.
2018-04-02 Added support for new shock pin specification convention.
2018-04-10 Support for nested group directories, but rejects not being merged correctly.
2018-04-19 Fixed typo in README
2018-04-27 Added baseplate layer for tapped holes + exploded that layer to two DXF formats, for Dan
2018-05-03 Changed choice.launch default to not save shock_currents.
2018-05-11 Calculating and reporting confidence intervals.
2018-05-14 Added exploded DXFs for top compression plate too.
2018-05-23 Removed asserts triggering in test of an odor against itself.
2018-05-24 Just finished most of refactoring, but included some hacks that will not work in general to get output for meeting. Just got it to run, need to check.
2018-05-30 Minimized number of holes and features in machined plates. Going with four corner holes to join each pair of plates.
2018-06-10 Simplified plot_trace, broke and fixing, will try to refactor load_metadata
2018-06-11 Seem to have somewhat accidentally fixed y offset issue. Not x though.
2018-06-16 Squash. Progress on metric code refactoring. Need to fix some DataFrame indexing. Fixed backend caused bug.
2018-06-21 Finished (hopefully still non-broken) MFC mounting plate. Working on similar mounts for rest of olfactometer.
2018-06-22 Started on mounts for humidifier in FreeCAD, but was having a hard time filleting the top plate, so I exported to DXF and did that in LibreCAD.
2018-06-25 Fixed error in MFC mounting hole layout.
2018-07-06 Fixed immediate bugs in case where there are no good flies.
2018-07-12 Fixed olfactometer inlet to box sides to be sufficiently high above chamber.
2018-07-30 First draft of top two layers for MAPLE loading.
2018-09-11 Fixed case odor breakdown in case where one odor has no good flies.
2018-09-25 Fixed crash when n=1 reporting CIs.
2018-10-29 Draft of MAPLE load/experiment/unload script.
2018-11-14 Flag to disable correction computation on one arena for now, for testing purposes on other.
2018-11-20 Widened fly loading holes on a ceiling for innate experiments (no contacts).
2018-12-01 More backlash aware calibration and moving. Fns to test doors. Support for new vent doors.
2018-12-14 Refactored calibration code a little and now visiting all vent doors more accurately, without as much manual correction.
2018-12-17 Refactored so most choice module fns take just a one dimensional index
